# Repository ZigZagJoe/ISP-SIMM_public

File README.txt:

_____  _____ _____        _____ _____ __  __ __  __ 
 |_   _|/ ____|  __ \      / ____|_   _|  \/  |  \/  |
   | | | (___ | |__) |____| (___   | | | \  / | \  / |
   | |  \___ \|  ___/______\___ \  | | | |\/| | |\/| |
  _| |_ ____) | |          ____) |_| |_| |  | | |  | |
 |_____|_____/|_|         |_____/|_____|_|  |_|_|  |_|
                                                                                                                                                      
     ZZJ ISP-SIMM v1.0
  by zigzagjoe (https://github.com/ZigZagJoe/ISP-SIMM_public)

-----------------------------------------------------
| Description                                       |
-----------------------------------------------------

This is a universal ROM SIMM for Apple Macintosh II and Quadra series computers, 
with a built-in USB programmer. It is intended to support rapid development 
of bare-metal code on Macintosh platforms.

This module has 16MB of total storage, exposed to the host 8MB at a time. 
Which half ("bank") the host 'sees' from is controlled by a switch on the module.

-----------------------------------------------------
| Basic operation                                   |
-----------------------------------------------------

1. Using appropriate ESD precautions, install the ROM SIMM in your Macintosh
2. Connect Micro USB cable to the module and your computer.
3. Copy a UF2 file to the ISP-SIMM drive to immediately write it to the active bank
4. Power on your Macintosh once the LED stops blinking and turns (dim) green

See following sections for how to convert .ROM to .UF2 format.

-----------------------------------------------------
| Notes/FAQ                                         |
-----------------------------------------------------

* This module is suitable for:
    Macintosh II series systems with a ROM slot
    Macintosh SE/30
    Quadra systems with a ROM slot (You may need to install a slot)
 
* Quadra's onboard ROMs are disabled if module is installed
    Remove the module to boot using onboard ROMs.
 
* USB does not need to be connected for the ROM module to function.
* USB may be plugged in or unplugged at any time regardless of Macintosh power state
 
* It is normal for the ISP-SIMM drive to briefly disappear and reappear after writing an image. 
    On some OS, this may complain that the drive was improperly ejected. This can be ignored.

* Select which bank the Macintosh will boot from using the switch on the top of the module
    You have two fully independent images that can accept 8MB images. 
    Do not change this switch while the mac is running or it will (almost certainly) crash.

* Do not use this module with any 3rd party ROM programmer devices
    It may cause damage to the module or the programmer.
	
* Apple ROM Flash utility and any other software flash utilities are not supported

*****************************************************
******************** IMPORTANT **********************
*****************************************************
* Any read of a UF2 file, or copy of UF2 file to the drive will disable the Macintosh's access to ROM. 
* This WILL crash the mac OR hold it in reset if the RESET_OUT connection is connected. 
*
* Once the operation finishes, the macintosh will be allowed to read again.
* The mac will automatically restart if the RESET_OUT has been connected.
*
* If you find the macintosh immediately crashes / resets when connecting USB, 
* check your virus scanner is not trying to scan the ISP-SIMM drive.
*****************************************************

-----------------------------------------------------
| UF2 File format                                   |
-----------------------------------------------------

This is the format used for reading and writing ROM images from the ISP-SIMM.
It is particularly suitable for use with microcontrollers due to self-contained data blocks.
It is an open format developed by Microsoft: https://github.com/microsoft/uf2/tree/master

--- Converting files ---

Two scripts have been provided with appropriate predefined settings. 

# Bin2UF2.PS1 (For Windows) 

Right-click, run with powershell, pick your input ROM file(s), and select your output directory.
It also supports command line arguments for batch processing / scripting: -Files and -Outdir
Report bugs to me.

# uf2conv.py (For Macintosh, Linux, or windows with Python3 installed) 

This will prompt interatively for a file (windows only), or accept a file on the command line.
Note: by default it will look for the ISP-SIMM drive and immediately begin flashing it if found. 
Please see here for more details: https://github.com/microsoft/uf2/blob/master/utils/uf2conv.md

# UF2 parameters for other tools

Model: ZZJ ISP-SIMM
Board-ID: ISP-SIMM-V1.0
UF2 Start Address: 0x0000 
UF2 Family ID: 0x10C68030

-----------------------------------------------------
| LED modes                                         |
-----------------------------------------------------

Dim Green               Power on, idle
Dim Red                 in Pico Bootloader mode (ROM is disabled)
Bright Red              Write failure occurred (invalid file or write was aborted)
Bright Green blinking   Read in progress
Bright Red blinking     Write in progress, errors have occurred
Green + Red blinking    Write in progress
Red flickering          USB->Serial TX or RX activity

Bright green solid / Green and Red solid / LEDs off: 
  host has stopped writing/reading, a time out will occur shortly.

-----------------------------------------------------
| USB terminal                                      |
-----------------------------------------------------

Open the USB serial port using your terminal software of choice, baud rate does not matter.
By default, log entries will be shown here as they occur.

Press ~~~ (3 tildes) and WAIT until "COMMAND?" is displayed before entering a command.
All other input will be forwarded to the UART header onboard.

--- Commands ---

echo 0|1     disable/enable debug logging to USB. 
  Required for running other protocols over USB-Serial
  This setting will be saved and used at next power-on of SIMM.

baud n       set serial uart baud rate to n
  Immediately change the uart's baud rate (this does no change anthing on the USB serial port)
  This setting will be saved and used at next power-on of SIMM.

bank a|b|c   set bank a|b or (c)lear to use switch's setting 
  Use to specify which bank is written when dragging a UF2 file to the drive, or what BANK_CUR.UF2 reads back.
  This will override the physical switch until the module is reset or "bank c" is issued

refresh      refresh drive contents to OS
  Causes the USB device to briefly eject and re-insert its media. 
  This forces most OS to update the contents of files and is performed automatically on writes.

bootloader   reboot to pico uf2 bootloader
  Immediately reboots to the pico's UF2 bootloader mode
  
resetmac     resets macintosh (requires RESET_OUT connection)
  Immediately resets the macintosh using the RESET_OUT connection.
  Ignored while ROM flashing or read operations are in progress.
   
showlog      prints recent log entries
  prints the log up until the most recent wrap point
  
Note: Commands with arguments will return the current status if run with no arguments.

-----------------------------------------------------
| Firmware updates                                  |
-----------------------------------------------------

Firmware is posted on github, at the link at the top of this document.
Please report issues there.

--- How to update ---

1. Shut down the mac and disconnect module from computer. 
2. Hold the "BOOTSEL" switch on the back of the module
3. Connect the module to the computer.
4. You should see a RPI-RP2 drive appear on the computer. You may release the BOOTSEL switch.
5. Drag the .uf2 file obtained from github to this drive.
6. The RPI-RP2 drive will disappear, and the ISP-SIMM drive should reappear.
     Your computer may complain about unclean ejection of drive. This can be ignored.
7. Verify new firmware version by checking INFO_UF2.TXT

--- Alternate method to enter bootloader ---

Issue the bootloader command from the USB serial terminal, then continue from step 4.

-----------------------------------------------------
| Troubleshooting                                   |
-----------------------------------------------------

--- Checking the log ---

Open ISP-SIMM.log in text editor of choice. This contains essential troubleshooting information.

NOTE: This log file DOES NOT UPDATE. This is an unavoidable limitation of how I present storage to the host.
To update this log: issue a "refresh" command via USB serial, write an image to the drive, or unplug/replug USB.

Note: More recent entries will begin overwriting old ones at the top of the log file.

I recommend that you use USB serial logging for realtime troubleshooting.

---------

No boot
    Verify the LED is DIM green after write completes (success)
	Verify the ROM is correctly seated. 
    If your ROM socket is unreliable or dirty, the module may need some pressure to correctly make contact.
    Make sure you're writing a ROM file that is compatible with your Macintosh
    ISP-SIMM expects ROM files in little endian byte order.
    Check the log for more information.
	
USB does not connect
	Try a different cable / use the cable supplied.
	Reflash firmware to SIMM

Write errors 
    Try again.
    Try connecting USB directly to computer.
    Try a different computer.
    As always, check the log.
 
Mac crashes / resets unexpectedly or when USB is plugged in
    Verify antivirus software is not scanning the ISP-SIMM drive
  
BANK_A.UF2 OR BANK_B.UF2 are 0 bytes in size
    A write error occurred the last time you were flashing this bank. 
    Please try again, and consult the log if issues continue.
 
BANK_CUR.UF2 is always 16MB in size
	This is expected. Due to limitations in how the USB mass storage works,
	it is not possible to read out anything but the full bank using BANK_CUR
	
Feel free to reach out to me on github or 68kmla with log files if you continue to have issues.

 ###################################################################################
#####################################################################################
###    / \     Scary message:                                                     ###
###   /   \                                                                       ###
###  /  !  \   Advanced functionality past this point. Proceed at your own risk!  ###
### /_______\  I take no responsibility if you damage your SIMM or Macintosh.     ###
#####################################################################################
 ###################################################################################
 
-----------------------------------------------------
| RESET_OUT header                                  |
-----------------------------------------------------

OPTIONAL. This allows the SIMM to automatically reset the Mac and hold it in reset 
while SIMM read/write operations are in progress. Open collector output, 5V logic safe. 

Connect to the a RESET pin (such as found on the reset button) or on a header (ie. Pin A12 of SE/30 PDS).

Make very certain you are connecting this correctly or you WILL cause damage 
to either the SIMM or your macintosh.

You can test by plugging the wire into the appropriate location on your logic board, 
and then connecting it to ground using a 100 - 1000 ohm resistor. 

Your system should reset and not boot until disconnected.

-----------------------------------------------------
| Serial (UART) header                              |
-----------------------------------------------------

The ISP-SIMM has a hardware UART exposed on the serial header. 

All UART data received is forwarded to USB serial, and all input to the USB serial 
is sent to the UART connected device. See above for configuration notes.

This is a SM04B-SURS type connector. Pin 1 is designated by a small triangle.

Pin 1: GND
Pin 2: Pico RX (Device TX)
Pin 3: Pico TX (Device RX)
Pin 4: +5V Power

*****************************************************
******************** IMPORTANT **********************
*****************************************************
* UART TX/RX pins are 3V logic. They are NOT 5V tolerant!!! 
* DO NOT connect +5V or 5V logic to TX or RX! You WILL damage your SIMM.
* A level converter (MAX3232) @ 3V is required to connect to Macintosh.
*
* I am sorry for providing +5V power and not +3.3V :(
*****************************************************

-----------------------------------------------------
| External USB                                      |
-----------------------------------------------------

USB pads are exposed on the bottom of the module so you may solder a USB cable (at your own risk!)

On the bottom of the Pico module: D+ is nearest to the -sign
On the bottom of the Pico module: D- is nearest to the +sign
+5V is immediately next to the +, over the PWRIN label
GND is immediately next to the -, over the PWRIN label

_____________________________________________________________
          \        _______    _______        /       
           \      |       |  |       |      /            ____  
            \     |   D-  |  |   D+  |     /            /
             \    |_______|  |_______|    /            /
              \__________________________/            /
                    ______    ______                 (    
             |     /      \  /      \                (    
           -----  |  +5V   ||   GND  |  ------        \ 
             |     \______/  \______/                  \
                                                        \____
                  P    W    R   I   N                    

-----------------------------------------------------
| External Bank Select Switch                       |
-----------------------------------------------------

You can use an external bank select switch so long as you leave the onboard switch in the B position.
Solder leads to the two pins that are shorted when the switch is in the A position.

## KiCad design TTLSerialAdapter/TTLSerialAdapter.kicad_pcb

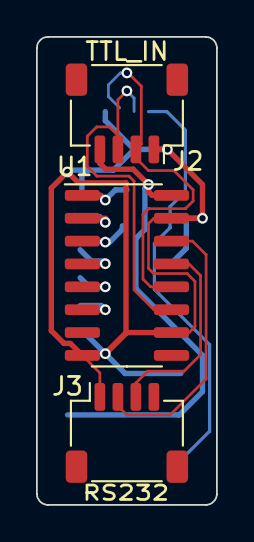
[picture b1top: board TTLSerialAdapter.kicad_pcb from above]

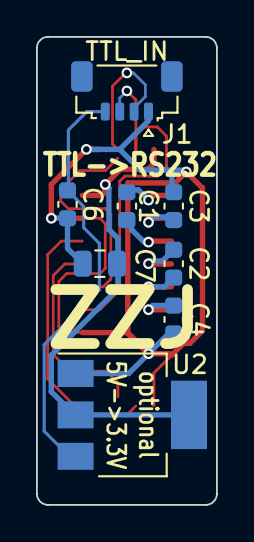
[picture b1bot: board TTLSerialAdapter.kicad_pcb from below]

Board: 2 copper layers, 10.0 x 26.0 mm, 11 parts (8 on the bottom side), 13 nets.

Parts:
C1, C2, C3, C4, C6: 100nF; C_0603_1608Metric
C7: 22uF; C_0805_2012Metric
J1: TTL_IN; JST_SUR_SM04B-SURS-TF_1x04-1MP_P0.80mm_Horizontal
J2: TTL_IN; JST_SH_SM04B-SRSS-TB_1x04-1MP_P1.00mm_Horizontal
J3: RS232; JST_SH_SM04B-SRSS-TB_1x04-1MP_P1.00mm_Horizontal
U1: MAX3232; SOIC-16_3.9x9.9mm_P1.27mm
U2: AMS1117-3.3; SOT-223-3_TabPin2

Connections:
+3V3: C7.1, J2.4, U1.16 (VCC), U2.2 (VO)
+5V: C6.2, J1.4, U2.3 (VI)
/RX_SER: J3.2, U1.14 (T1OUT)
/RX_TTL: J1.2, J2.2, U1.12 (R1OUT)
/TX_SER: J3.3, U1.13 (R1IN)
/TX_TTL: J1.3, J2.3, U1.11 (T1IN)
GND: C3.2, C4.2, C6.1, C7.2, J1.1, J2.1, J3.1, U1.8 (R2IN), U1.10 (T2IN), U1.15 (GND), U2.1 (GND)
unnamed: C1.1, U1.1 (C1+)
unnamed: C1.2, U1.3 (C1-)
unnamed: C2.1, U1.4 (C2+)
unnamed: C2.2, U1.5 (C2-)
unnamed: C3.1, U1.2 (VS+)
unnamed: C4.1, U1.6 (VS-)

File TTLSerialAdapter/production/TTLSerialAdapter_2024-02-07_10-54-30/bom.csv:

Designator,Footprint,Quantity,Value,LCSC Part #
"C1, C2, C3, C4",0603,4,100nF,C14663
C7,0805,1,22uF,C45783
J1,JST_SUR_SM04B-SURS-TF_1x04-1MP_P0.80mm_Horizontal,1,TTL_IN,N/A
J2,JST_SH_SM04B-SRSS-TB_1x04-1MP_P1.00mm_Horizontal,1,TTL_IN,
J3,JST_SH_SM04B-SRSS-TB_1x04-1MP_P1.00mm_Horizontal,1,RS232,N/A
U1,SOIC-16_3.9x9.9mm_P1.27mm,1,MAX3232,

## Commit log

2024-01-20 Update for build 61
2024-01-20 Update for build 62
2024-01-21 Update for build 79
2024-01-22 Update for build 86
2024-01-23 Update for build 101
2024-01-23 Update for build 102
2024-01-23 Update for build 104
2024-01-23 Update for build 106
2024-01-29 Update for build 113
2024-02-11 Update for build 115
2024-02-13 Update for build 116
2025-01-13 Update for build 120
2025-04-13 Update for build 121
2025-06-14 add TTL serial adapter
2025-11-13 Add production files
2026-02-22 Recessed bank select switch
